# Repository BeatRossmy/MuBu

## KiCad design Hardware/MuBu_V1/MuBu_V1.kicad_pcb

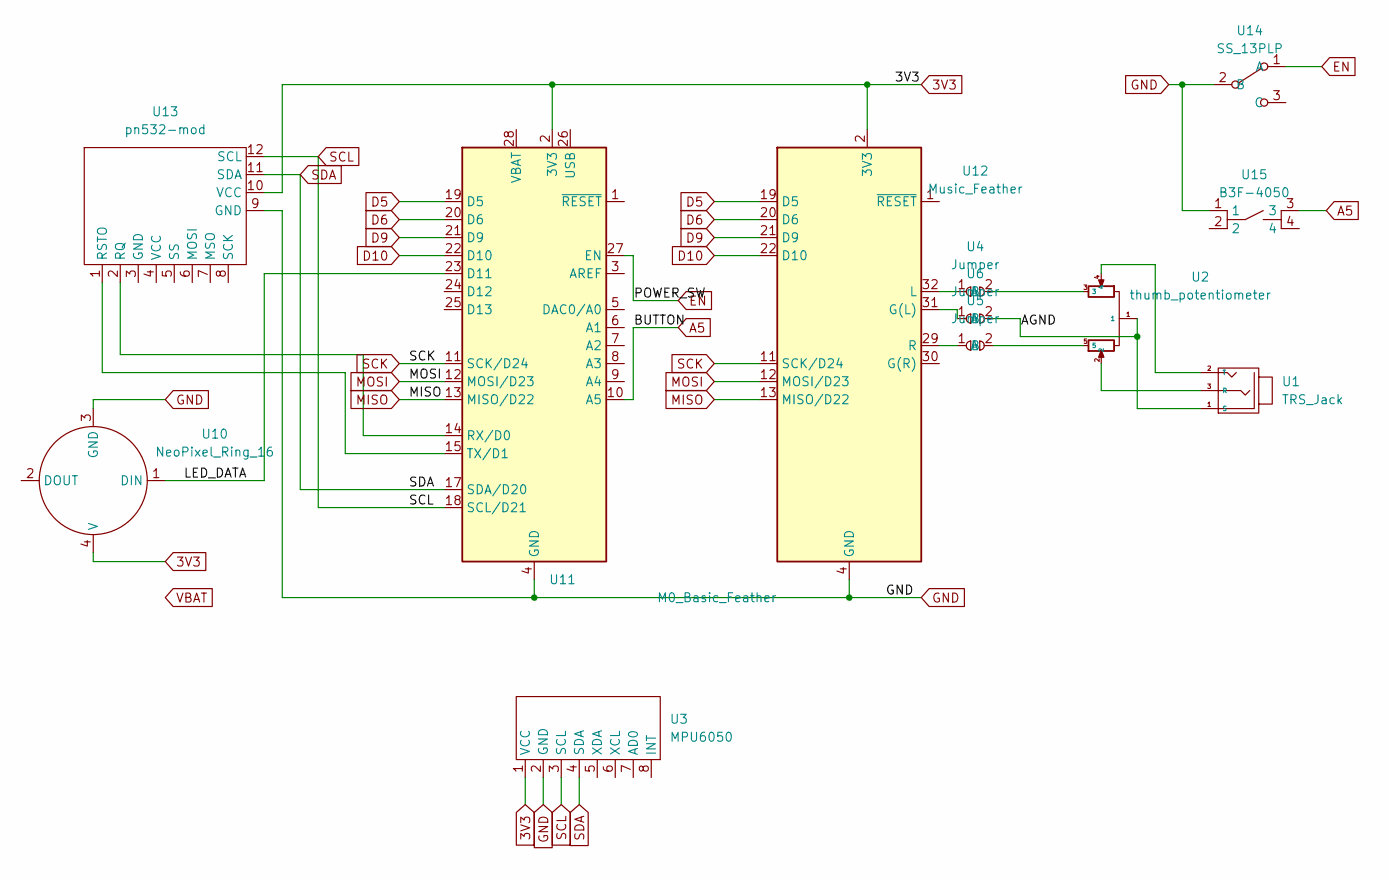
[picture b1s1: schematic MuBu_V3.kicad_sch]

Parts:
U1: TRS_Jack; STX-3501
U2: thumb_potentiometer
U3: MPU6050
U4, U5, U6: Jumper
U10: NeoPixel_Ring_16; neopixel_ring_16
U11: M0_Basic_Feather
U12: Music_Feather
U13: pn532-mod; PN532-MOD
U14: SS_13PLP
U15: B3F-4050

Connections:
3V3: U3.1 (VCC), U10.4 (V), U11.2 (3V3), U12.2 (3V3), U13.10 (VCC)
/AGND: U1.1 (S), U2.1, U6.2 (B)
/LED_DATA: U10.1 (DIN), U11.23 (D11)
A5: U11.10 (A5), U15.3
D5: U11.19 (D5), U12.19 (D5)
D6: U11.20 (D6), U12.20 (D6)
D9: U11.21 (D9), U12.21 (D9)
D10: U11.22 (D10), U12.22 (D10)
EN: U11.27 (EN), U14.1 (A)
GND: U3.2 (GND), U10.3 (GND), U11.4 (GND), U11.16 (GND), U12.4 (GND), U12.16 (GND), U13.9 (GND), U14.2 (B), U15.1
MISO: U11.13 (MISO/D22), U12.13 (MISO/D22)
MOSI: U11.12 (MOSI/D23), U12.12 (MOSI/D23)
unnamed: U1.2 (T), U2.4
unnamed: U1.3 (R), U2.2
unnamed: U2.3, U4.2 (B)
unnamed: U2.5, U5.2 (B)
unnamed: U11.14 (RX/D0), U13.2 (RQ)
unnamed: U11.15 (TX/D1), U13.1 (RSTO)
unnamed: U5.1 (A), U12.29 (R)
unnamed: U6.1 (A), U12.31 (G(L))
unnamed: U4.1 (A), U12.32 (L)
SCK: U11.11 (SCK/D24), U12.11 (SCK/D24)
SCL: U3.3 (SCL), U11.18 (SCL/D21), U13.12 (SCL)
SDA: U3.4 (SDA), U11.17 (SDA/D20), U13.11 (SDA)

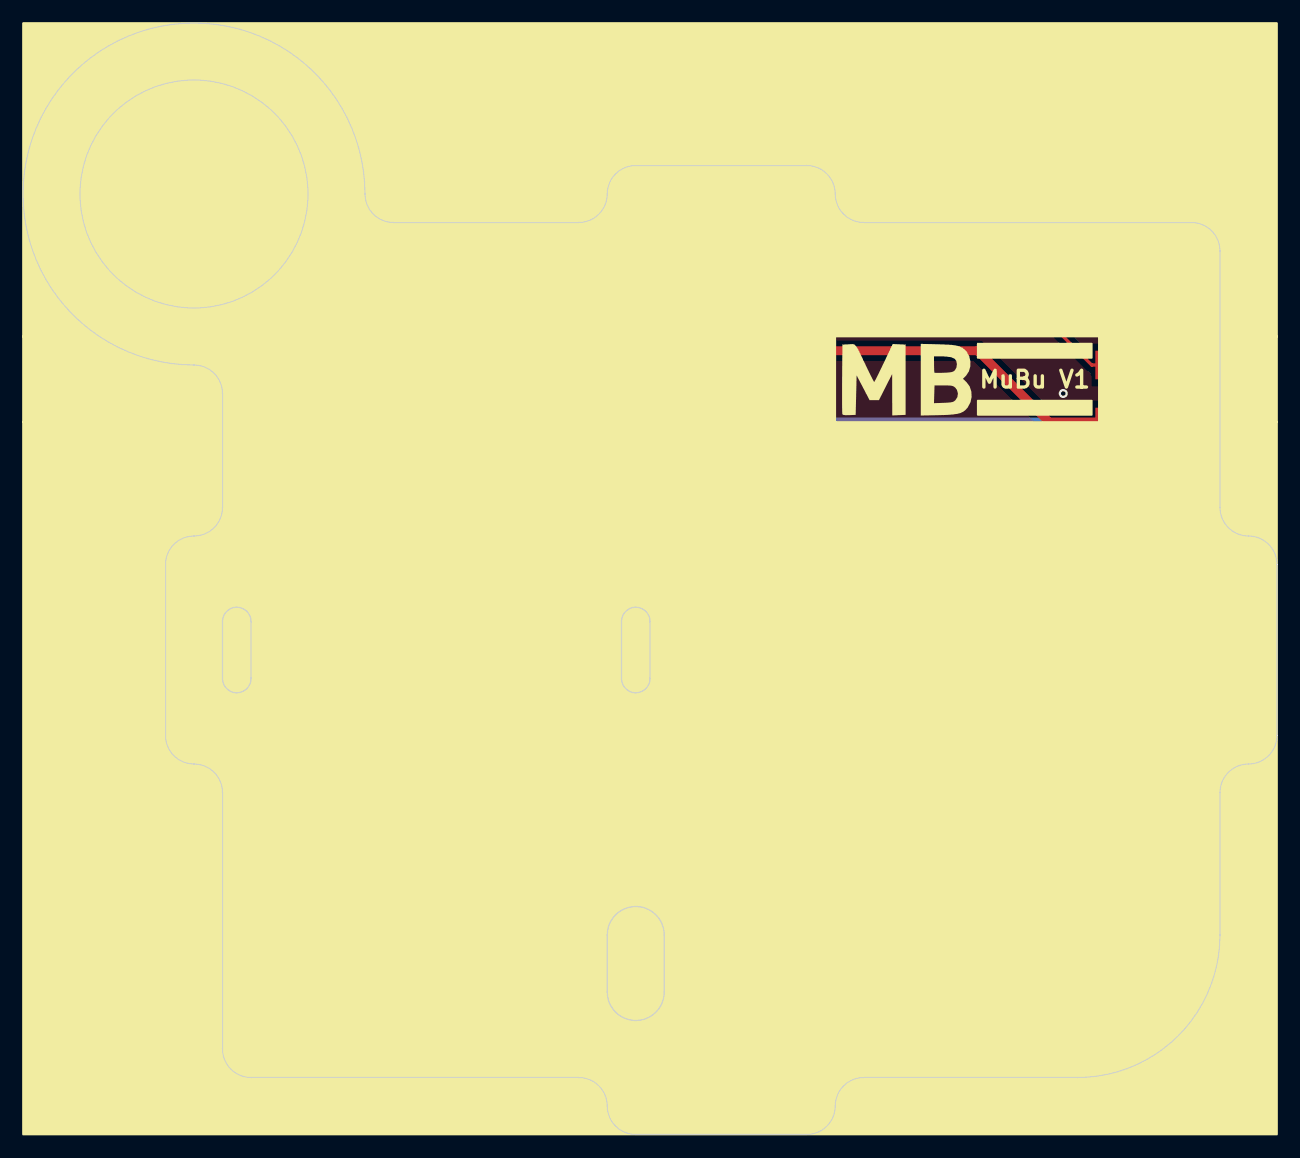
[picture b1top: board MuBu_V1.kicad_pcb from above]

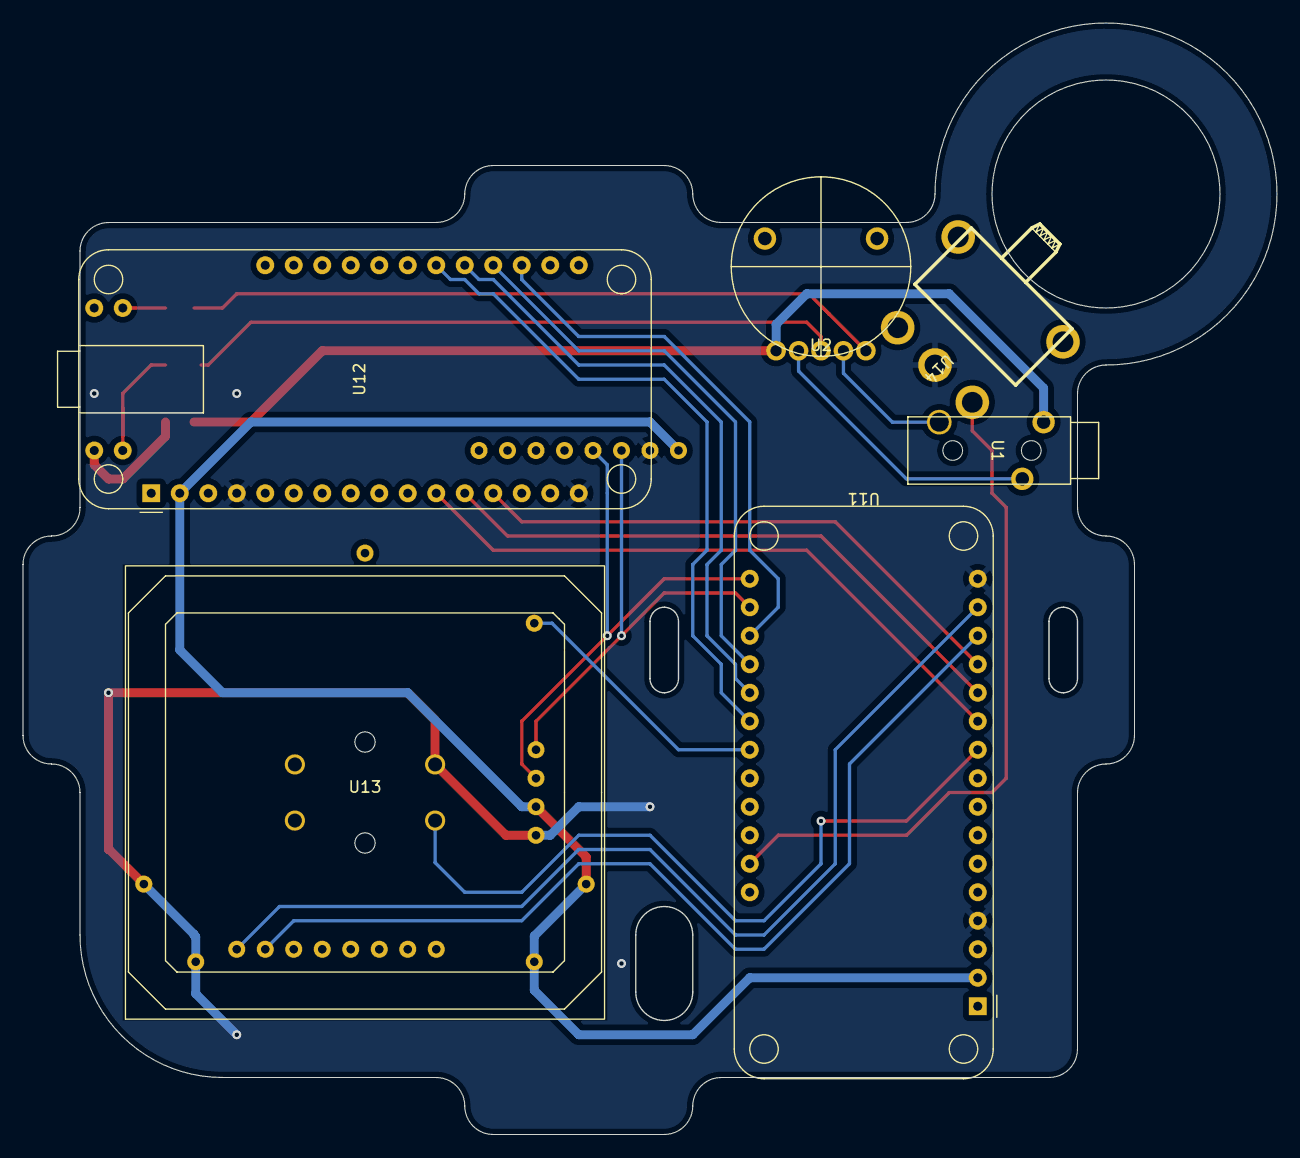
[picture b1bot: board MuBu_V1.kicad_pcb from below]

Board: 2 copper layers, 111.8 x 99.1 mm, 12 parts (6 on the bottom side), 24 nets.
